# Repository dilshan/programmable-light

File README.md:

# Programmable Light Controller

Programmable light is a low cost and easy to build LED light controller. The main objective of this project is to design a maintenance free light which automatically on and off at the predetermined time of the day.

This light controller is based on *ATmega8* microcontroller and *DS1307* real time clock. It is designed to handle commonly available 24V - 7W LED modules. 

This is [certified open source hardware project](https://certification.oshwa.org/lk000002.html). All the design files, documentation, firmware source code are available to download at the [project source repository](https://github.com/dilshan/programmable-light). All the content of this project are distributed under the terms of the following license: 

* Hardware License: [CC BY 4.0](https://creativecommons.org/licenses/by/4.0/)
* Software License: [MIT](https://github.com/dilshan/programmable-light/blob/master/LICENSE)
* Documentation License: [CC BY 4.0](https://creativecommons.org/licenses/by/4.0/)

For more details check [project documentation at GitHub](https://github.com/dilshan/programmable-light/wiki).

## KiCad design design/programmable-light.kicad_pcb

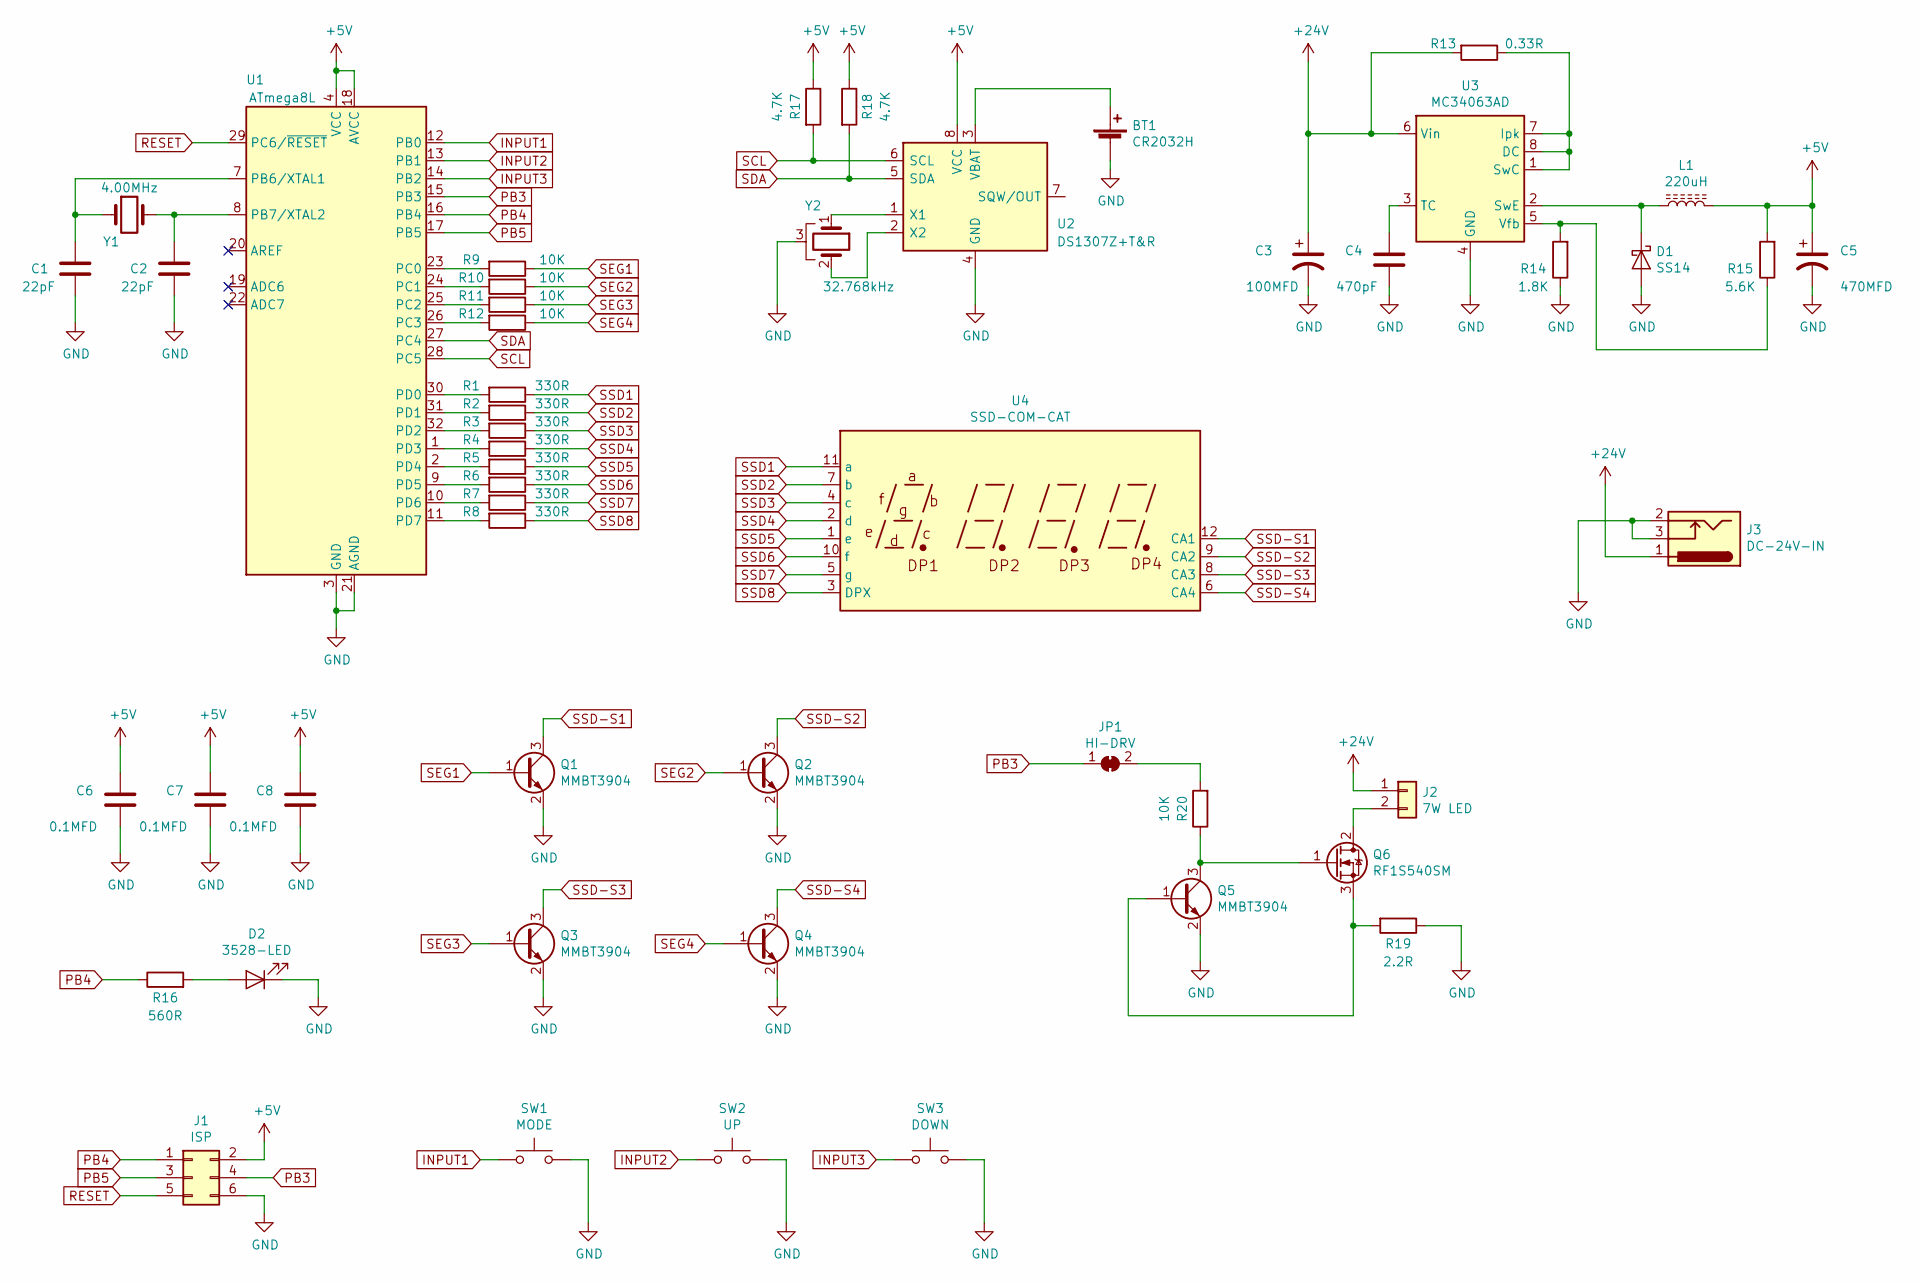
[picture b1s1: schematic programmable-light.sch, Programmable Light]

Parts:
BT1: CR2032H; BatteryHolder_Keystone_104_1x23mm
C1, C2: 22pF; C_0805_2012Metric
C3: 100MFD; CP_Elec_6.3x5.4
C4: 470pF; C_0805_2012Metric
C5: 470MFD; CP_Elec_10x10.5
C6, C7, C8: 0.1MFD; C_0805_2012Metric
D1: SS14; D_SMA
D2: 3528-LED; LED_1210_3225Metric
J1: ISP; PinHeader_2x03_P2.54mm_Vertical
J2: 7W LED; PhoenixContact_MCV_1,5_2-G-3.81_1x02_P3.81mm_Vertical
J3: DC-24V-IN; BarrelJack_Horizontal
JP1: HI-DRV; SolderJumper-2_P1.3mm_Bridged2Bar_RoundedPad1.0x1.5mm
L1: 220uH; L_Taiyo-Yuden_NR-80xx
Q1, Q2, Q3, Q4, Q5: MMBT3904; SOT-23
Q6: RF1S540SM; TO-263-2
R1, R2, R3, R4, R5, R6, R7, R8: 330R; R_0805_2012Metric
R9, R10, R11, R12, R20: 10K; R_0805_2012Metric
R13: 0.33R; R_2512_6332Metric
R14: 1.8K; R_0805_2012Metric
R15: 5.6K; R_0805_2012Metric
R16: 560R; R_0805_2012Metric
R17, R18: 4.7K; R_0805_2012Metric
R19: 2.2R; R_Axial_DIN0516_L15.5mm_D5.0mm_P20.32mm_Horizontal
SW1: MODE; SW_PUSH_6mm
SW2: UP; SW_PUSH_6mm
SW3: DOWN; SW_PUSH_6mm
U1: ATmega8L; TQFP-32_7x7mm_P0.8mm
U2: DS1307Z+T&R; SOIC-8_3.9x4.9mm_P1.27mm
U3: MC34063AD; SOIC-8_3.9x4.9mm_P1.27mm
U4: SSD-COM-CAT; CA56-12CGKWA
Y1: 4.00MHz; Crystal_SMD_HC49-SD
Y2: 32.768kHz; Crystal_C26-LF_D2.1mm_L6.5mm_Horizontal_1EP_style2

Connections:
+5V: C5.1, C6.1, C7.1, C8.1, J1.2, L1.2, R15.2, R17.1, R18.1, U1.4 (VCC), U1.6 (VCC), U1.18 (AVCC), U2.8 (VCC)
+24V: C3.1, J2.1, J3.1, R13.2, U3.6 (Vin)
GND: BT1.2 (-), C1.2, C2.2, C3.2, C4.2, C5.2, C6.2, C7.2, C8.2, D1.2 (A), D2.1 (K), J1.6, J3.2, J3.3, Q1.2 (E), Q2.2 (E), Q3.2 (E), Q4.2 (E), Q5.2 (E), R14.1, R19.1, SW1.2, SW2.2, SW3.2, U1.3 (GND), U1.5 (GND), U1.21 (AGND), U2.4 (GND), U3.4 (GND), Y2.3
INPUT1: SW1.1, U1.12 (PB0)
INPUT2: SW2.1, U1.13 (PB1)
INPUT3: SW3.1, U1.14 (PB2)
unnamed: BT1.1 (+), U2.3 (VBAT)
unnamed: C1.1, U1.7 (PB6/XTAL1), Y1.1
unnamed: C2.1, U1.8 (PB7/XTAL2), Y1.2
unnamed: C4.1, U3.3 (TC)
unnamed: D1.1 (K), L1.1, U3.2 (SwE)
unnamed: D2.2 (A), R16.2
unnamed: J2.2, Q6.2 (D)
unnamed: JP1.2 (B), R20.2
unnamed: Q5.1 (B), Q6.3 (S), R19.2
unnamed: Q5.3 (C), Q6.1 (G), R20.1
unnamed: R1.2, U1.30 (PD0)
unnamed: R2.2, U1.31 (PD1)
unnamed: R3.2, U1.32 (PD2)
unnamed: R4.2, U1.1 (PD3)
unnamed: R5.2, U1.2 (PD4)
unnamed: R6.2, U1.9 (PD5)
unnamed: R7.2, U1.10 (PD6)
unnamed: R8.2, U1.11 (PD7)
unnamed: R9.2, U1.23 (PC0)
unnamed: R10.2, U1.24 (PC1)
unnamed: R11.2, U1.25 (PC2)
unnamed: R12.2, U1.26 (PC3)
unnamed: R13.1, U3.1 (SwC), U3.7 (Ipk), U3.8 (DC)
unnamed: R14.2, R15.1, U3.5 (Vfb)
unnamed: U2.1 (X1), Y2.1
unnamed: U2.2 (X2), Y2.2
PB3: J1.4, JP1.1 (A), U1.15 (PB3)
PB4: J1.1, R16.1, U1.16 (PB4)
PB5: J1.3, U1.17 (PB5)
RESET: J1.5, U1.29 (PC6/~RESET)
SCL: R17.2, U1.28 (PC5), U2.6 (SCL)
SDA: R18.2, U1.27 (PC4), U2.5 (SDA)
SEG1: Q1.1 (B), R9.1
SEG2: Q2.1 (B), R10.1
SEG3: Q3.1 (B), R11.1
SEG4: Q4.1 (B), R12.1
SSD1: R1.1, U4.11 (a)
SSD2: R2.1, U4.7 (b)
SSD3: R3.1, U4.4 (c)
SSD4: R4.1, U4.2 (d)
SSD5: R5.1, U4.1 (e)
SSD6: R6.1, U4.10 (f)
SSD7: R7.1, U4.5 (g)
SSD8: R8.1, U4.3 (DPX)
SSD-S1: Q1.3 (C), U4.12 (CA1)
SSD-S2: Q2.3 (C), U4.9 (CA2)
SSD-S3: Q3.3 (C), U4.8 (CA3)
SSD-S4: Q4.3 (C), U4.6 (CA4)

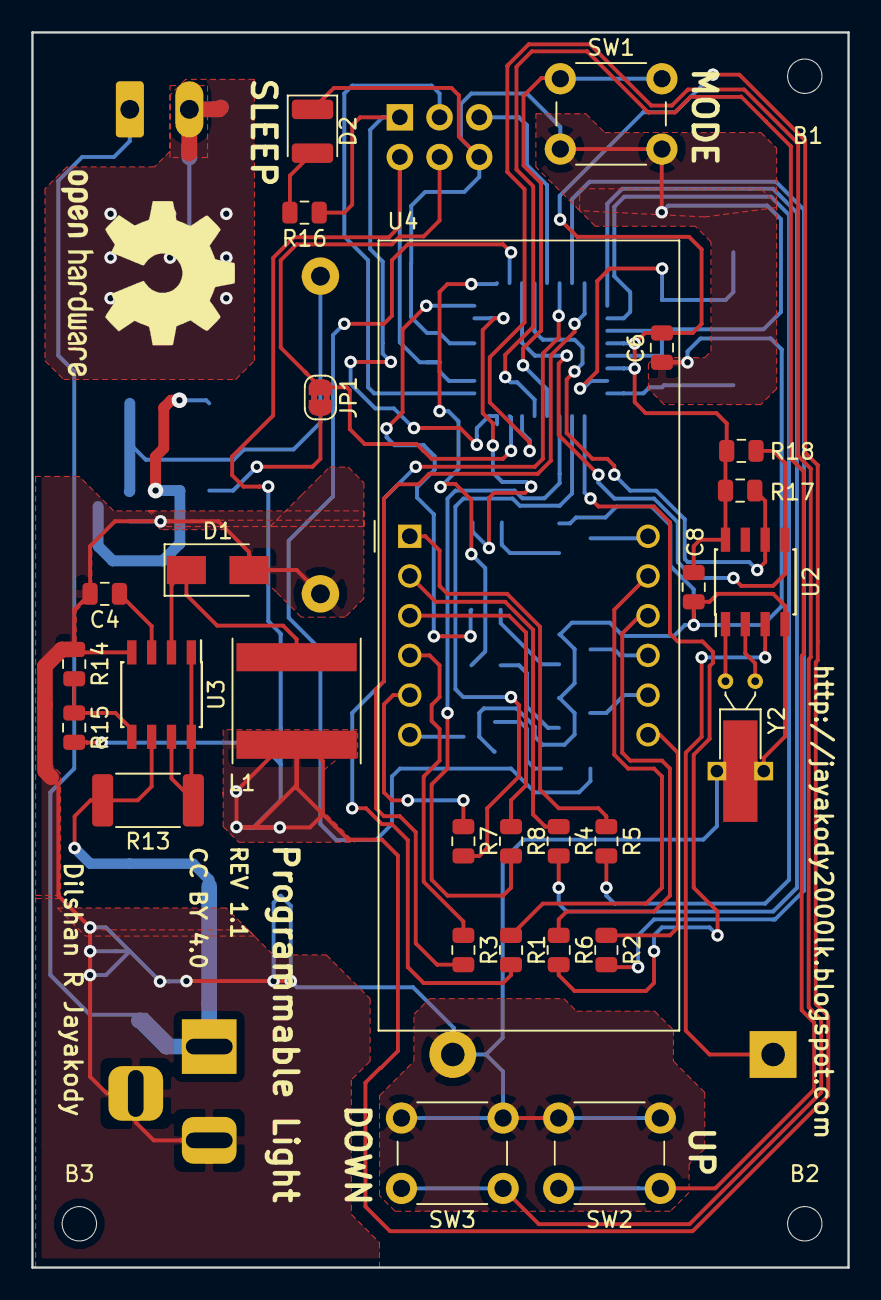
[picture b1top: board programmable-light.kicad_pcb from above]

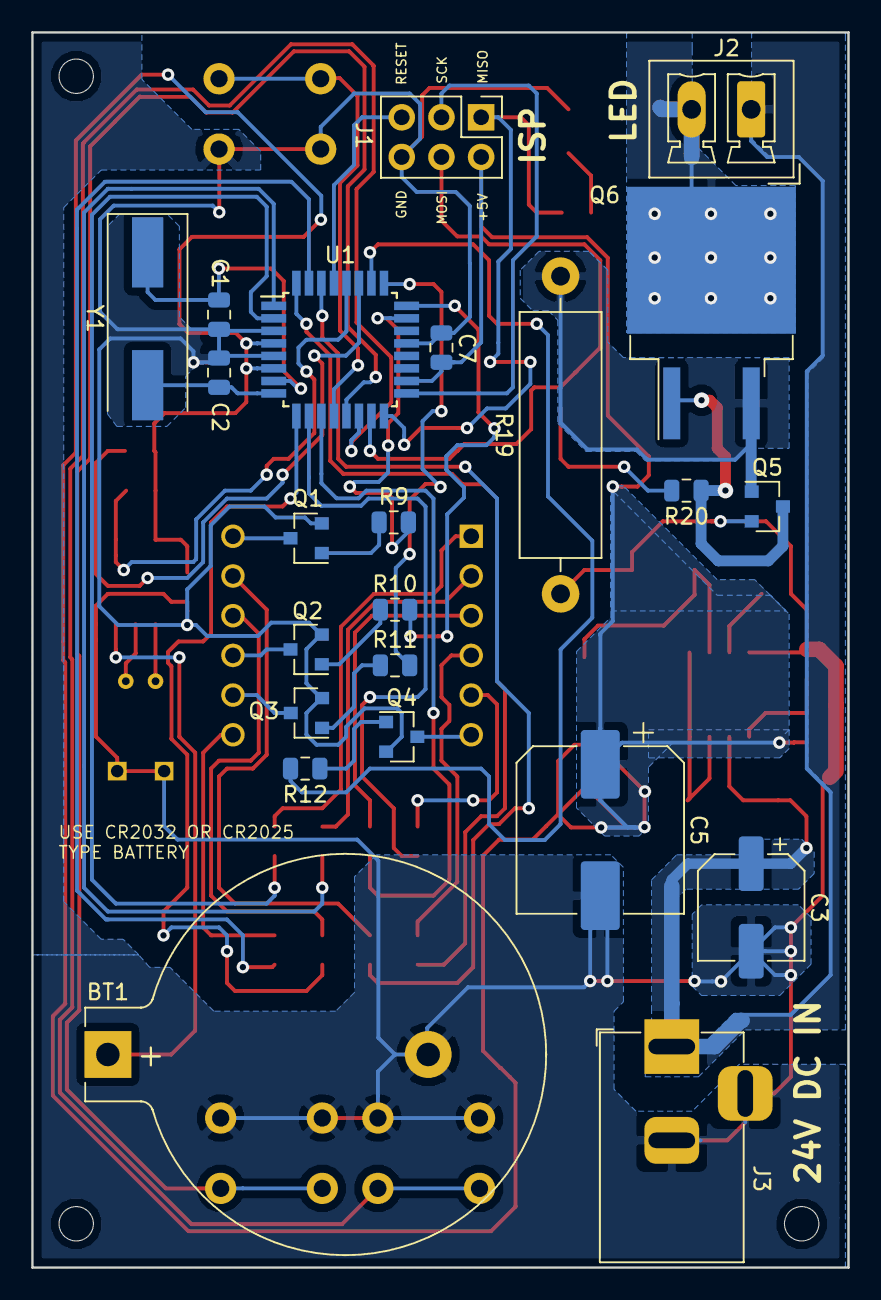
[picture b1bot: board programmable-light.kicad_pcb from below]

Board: 2 copper layers, 52.2 x 79.0 mm, 54 parts (23 on the bottom side), 54 nets.

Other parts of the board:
B1, B2, B3: M2-1; MountingHole_2.2mm_M2

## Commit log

2019-03-20 Initial version of firmware and design files.
2019-03-20 Fix broken links in readme file.
2019-03-21 Update readme document with project details.
2019-03-21 Update source file headers with github link.
2019-03-25 Add license statement into the documentation.
2019-03-26 Include OSHW logo and link into the documentation.
2019-03-26 Fix error in OSHW certificate image.
2019-03-26 Add link to OSHW certificate page.

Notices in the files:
design/programmable-light.kicad_pcb:
This work is released under the Creative Commons Attribution 4.0 International.
